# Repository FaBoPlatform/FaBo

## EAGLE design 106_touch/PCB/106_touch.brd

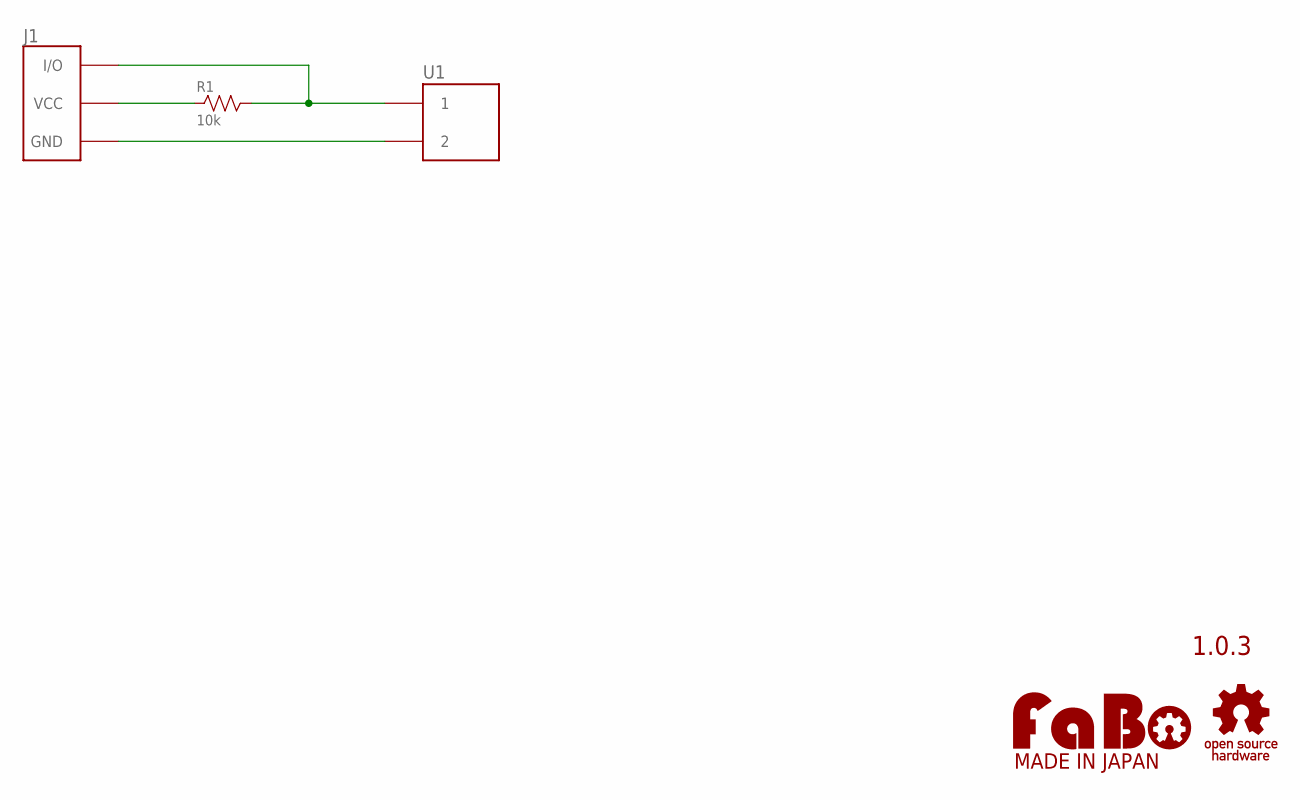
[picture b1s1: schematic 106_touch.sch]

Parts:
J1: FABO_BRICK_3PIN
R1: 10k; AXL-REGULAR
U1: FSR402-SHORT
U$2: LOGO_OSHW-M_BOTTOM; LOGO_OSHW_M_BOTTOM
U$3: LOGO_FABO-M; LOGO_FABO_MS

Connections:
GND: J1.GND, U1.P$2 (2)
unnamed: J1.I/O, R1.2, U1.P$1 (1)
unnamed: J1.VCC, R1.1

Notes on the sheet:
1.0.3

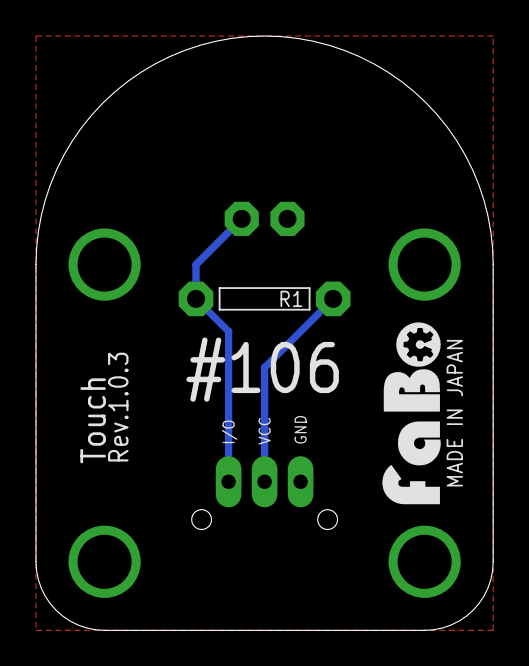
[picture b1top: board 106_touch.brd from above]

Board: 2 copper layers, 25.4 x 33.0 mm, 5 parts (0 on the bottom side), 3 nets.

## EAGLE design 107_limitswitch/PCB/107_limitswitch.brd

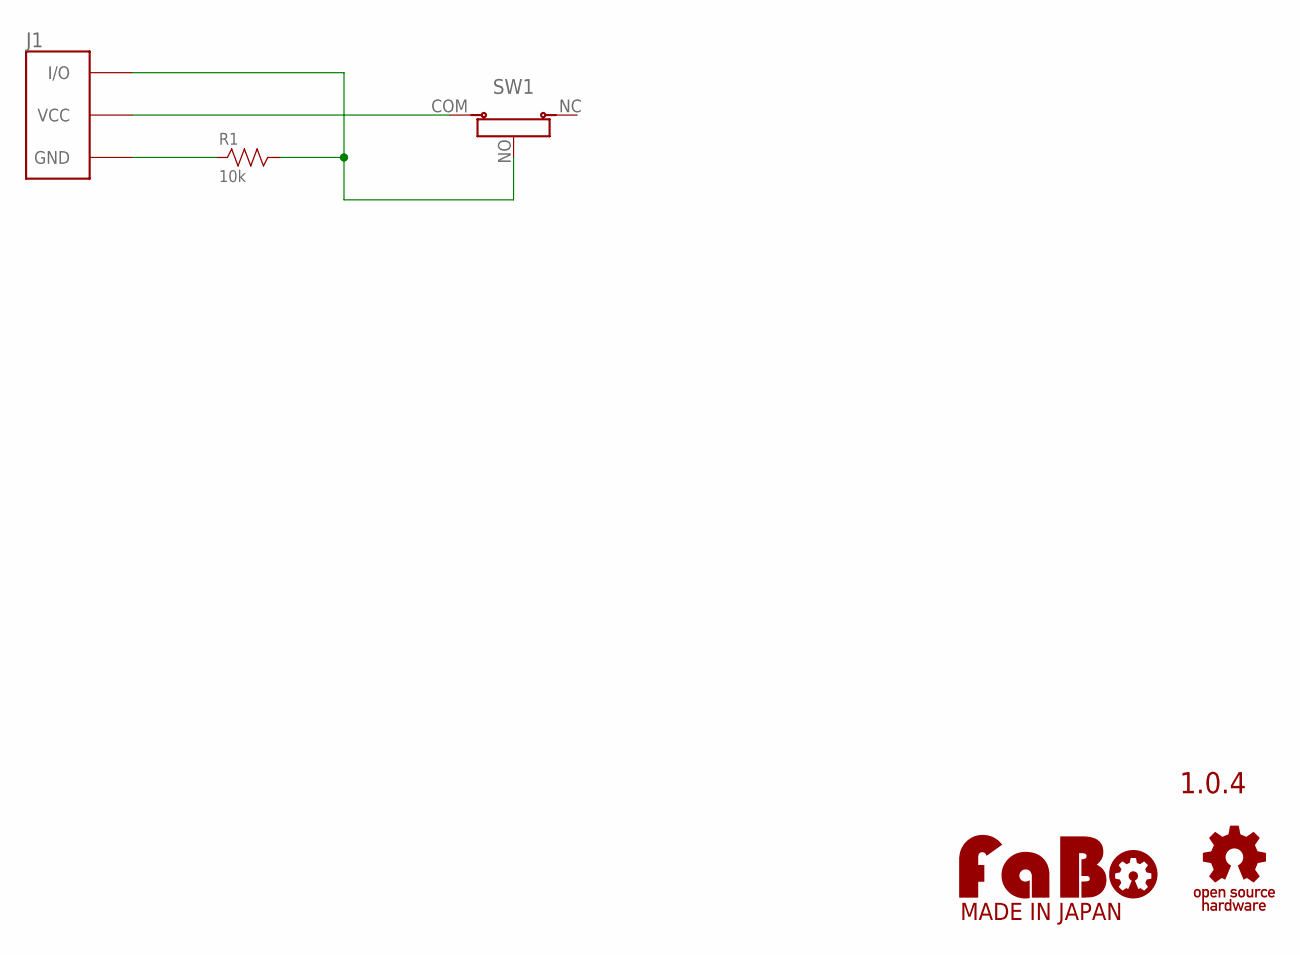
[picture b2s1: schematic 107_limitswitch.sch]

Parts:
J1: FABO_BRICK_3PIN
R1: 10k; AXL-REGULAR
SW1: LIMIT-SWITCH
U$2: LOGO_OSHW-M_BOTTOM; LOGO_OSHW_M_BOTTOM
U$4: LOGO_FABO-M; LOGO_FABO_MS

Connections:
GND: J1.GND, R1.1
unnamed: J1.VCC, SW1.COM (VCC)
unnamed: J1.I/O, R1.2, SW1.NO

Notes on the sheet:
1.0.4

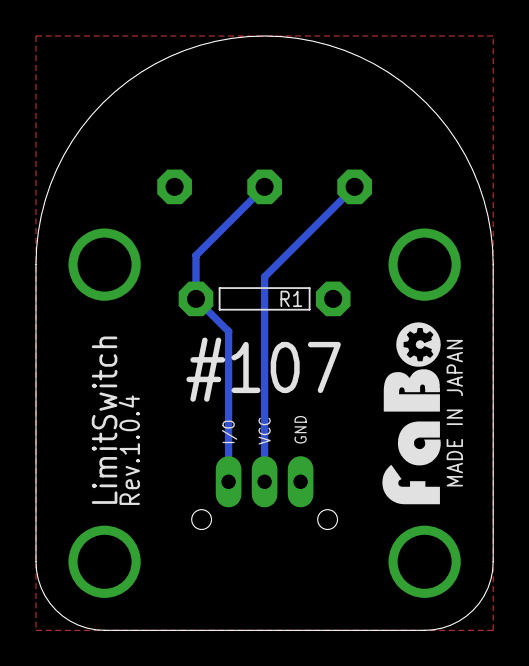
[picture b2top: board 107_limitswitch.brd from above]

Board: 2 copper layers, 25.4 x 33.0 mm, 5 parts (0 on the bottom side), 3 nets.

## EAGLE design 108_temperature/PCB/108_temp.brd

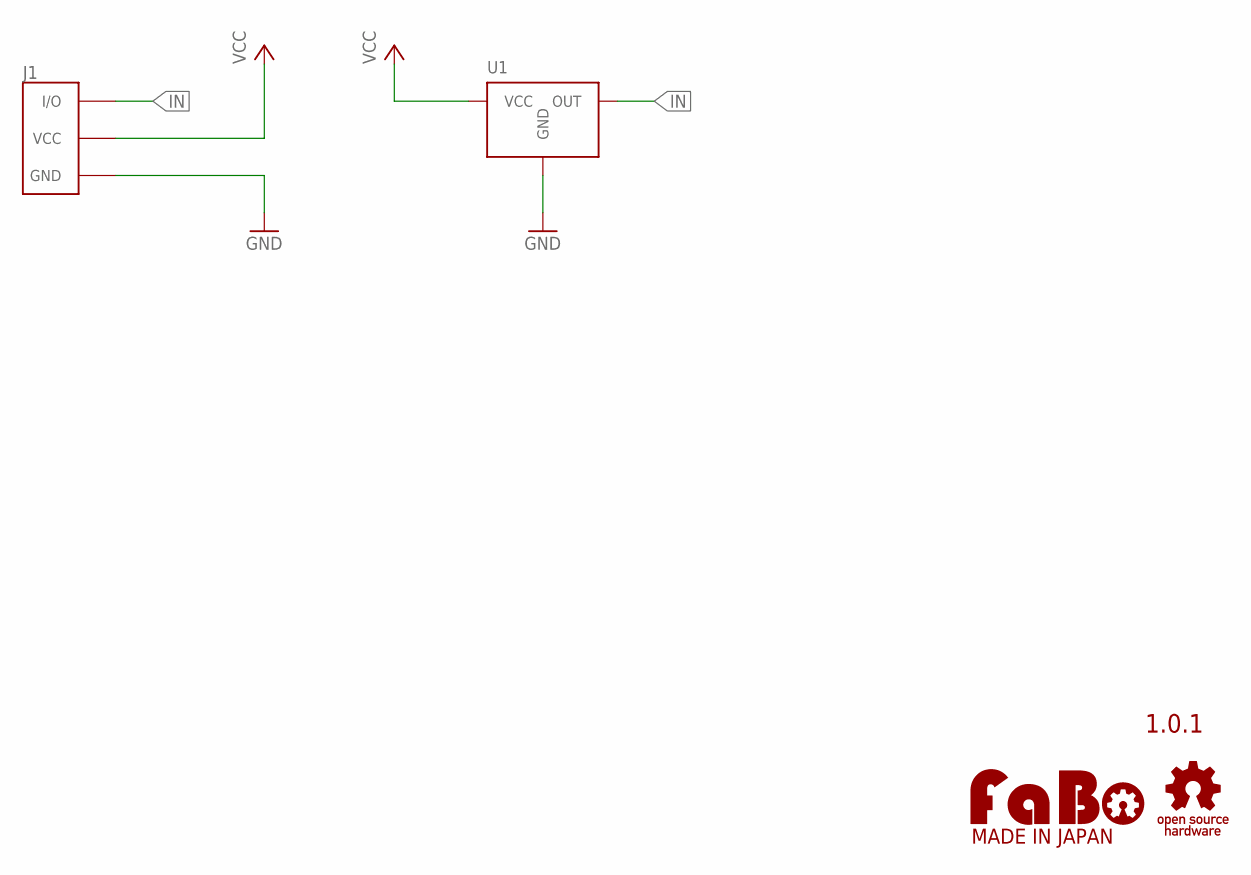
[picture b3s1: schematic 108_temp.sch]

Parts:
J1: FABO_BRICK_3PIN
U1: SENSOR-LM60-TO92; SENSOR-LM60-TO-92
U$2: LOGO_OSHW-T_M_BOTTOM; LOGO_OSHW_T_MS_BOTTOM
U$3: LOGO_FABO-M; LOGO_FABO_MS

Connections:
GND: J1.GND, U1.GND
IN: J1.IN/OUT (I/O), U1.OUT
VCC: J1.VCC, U1.VCC

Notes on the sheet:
1.0.1

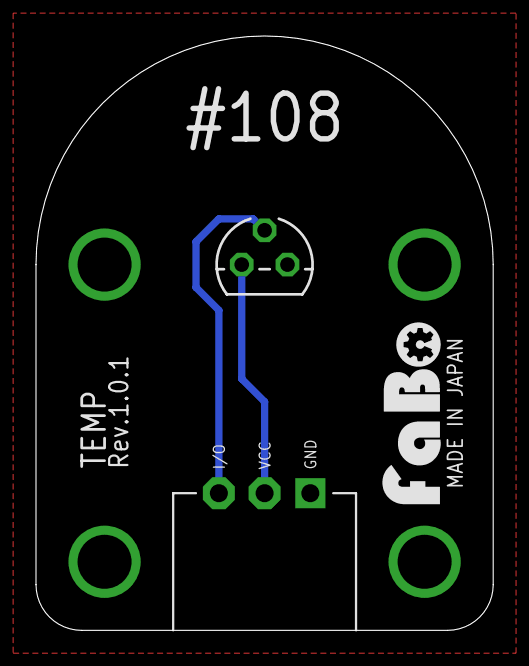
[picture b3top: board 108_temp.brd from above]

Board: 2 copper layers, 25.4 x 33.0 mm, 4 parts (0 on the bottom side), 3 nets.

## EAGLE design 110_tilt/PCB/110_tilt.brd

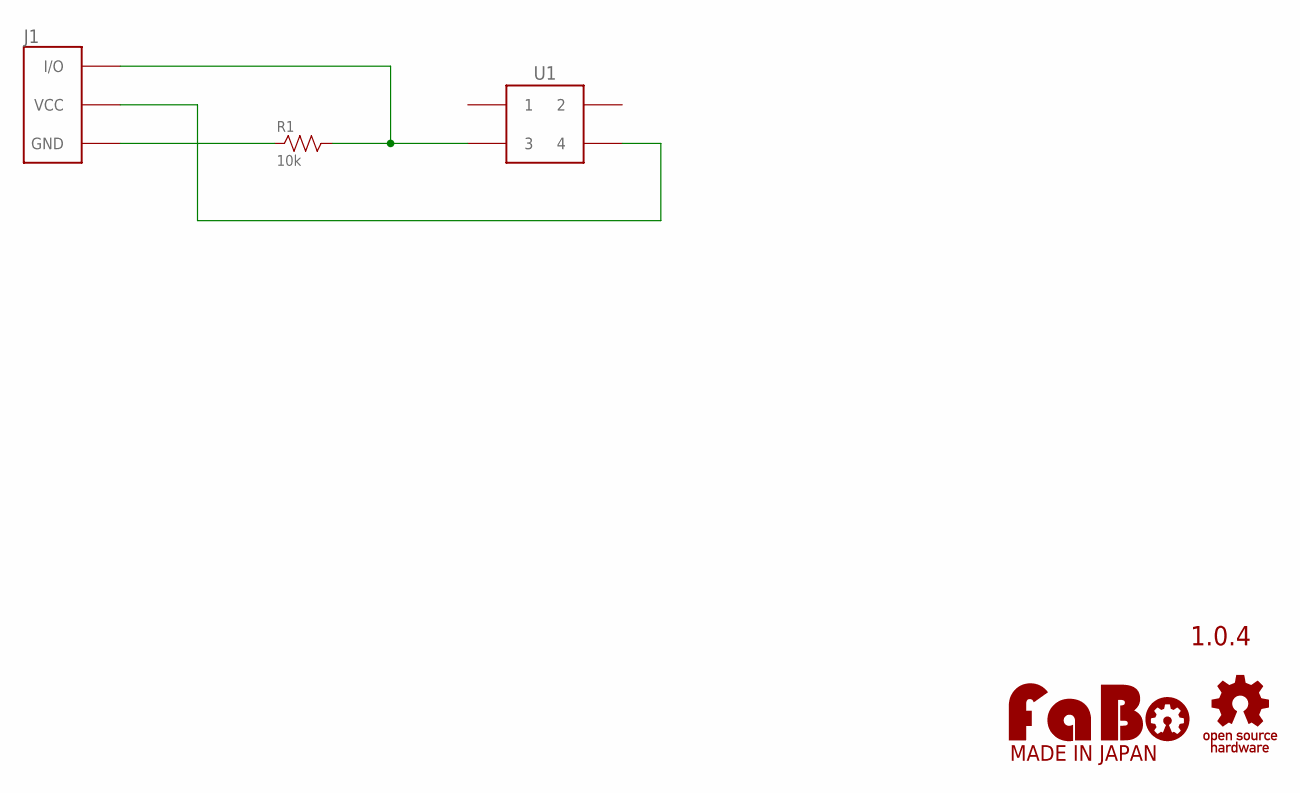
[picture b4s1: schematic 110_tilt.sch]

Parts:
J1: FABO_BRICK_3PIN
R1: 10k; AXL-REGULAR
U1: TILT; RBS040200
U$2: LOGO_OSHW-M_BOTTOM; LOGO_OSHW_M_BOTTOM
U$3: LOGO_FABO-M; LOGO_FABO_MS

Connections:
GND: J1.GND, R1.1
unnamed: J1.I/O, R1.2, U1.3
unnamed: J1.VCC, U1.4

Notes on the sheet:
1.0.4

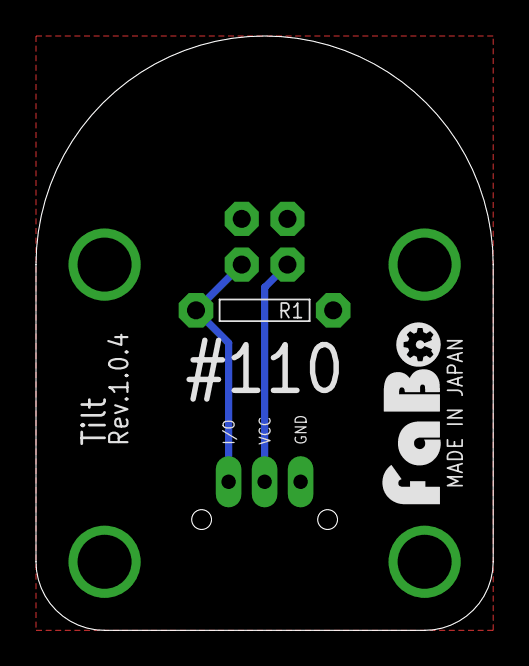
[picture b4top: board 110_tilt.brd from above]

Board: 2 copper layers, 25.4 x 33.0 mm, 5 parts (0 on the bottom side), 3 nets.

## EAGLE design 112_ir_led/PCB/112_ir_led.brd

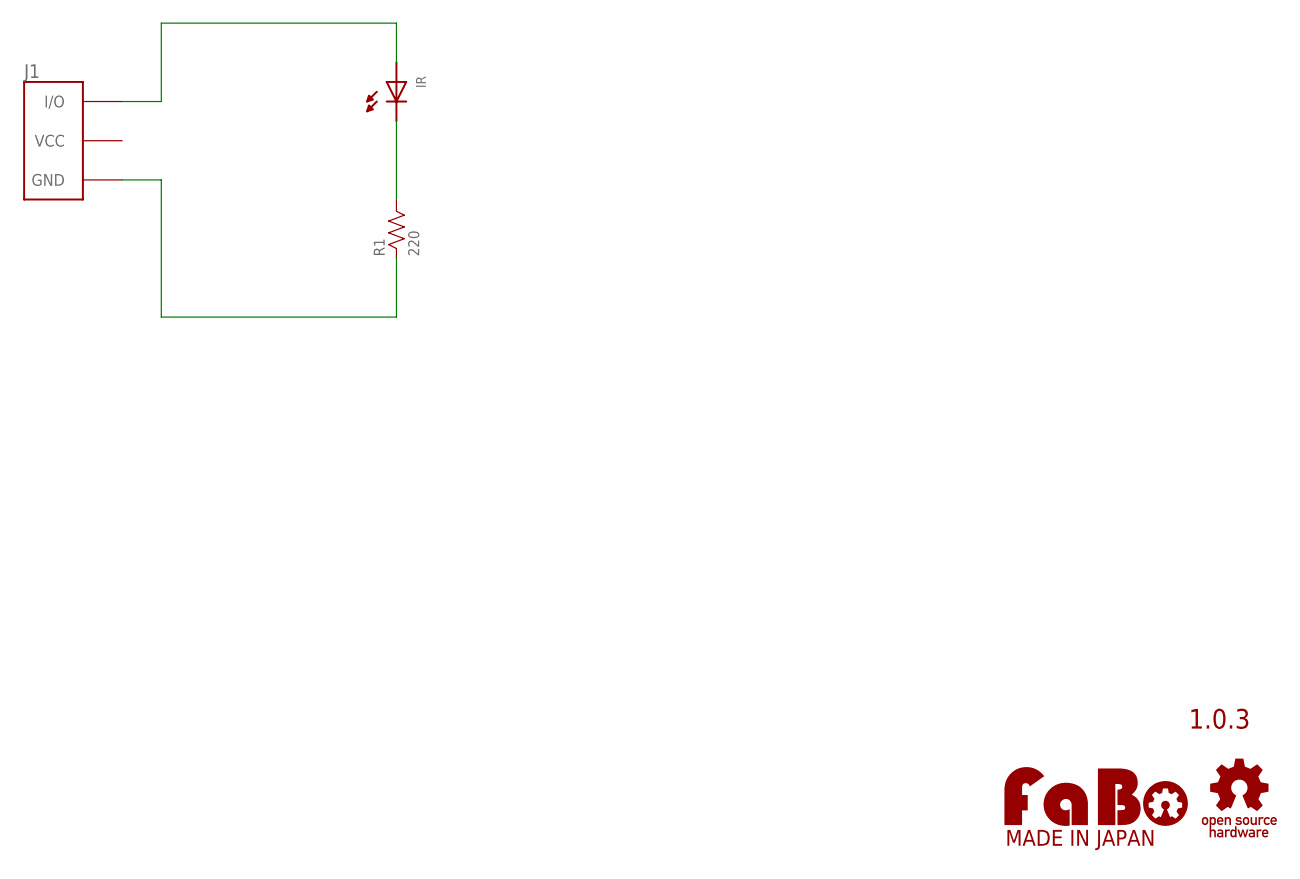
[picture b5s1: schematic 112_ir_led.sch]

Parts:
IR: LED-5MM; LED_5MM
J1: FABO_BRICK_3PIN
R1: 220; AXL-REGULAR
U$2: LOGO_FABO-M; LOGO_FABO_MS
U$3: LOGO_OSHW-M_BOTTOM; LOGO_OSHW_M_BOTTOM

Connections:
GND: J1.GND, R1.1
unnamed: IR.A (ANODE), J1.I/O
unnamed: IR.K (CATHODE), R1.2

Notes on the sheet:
1.0.3

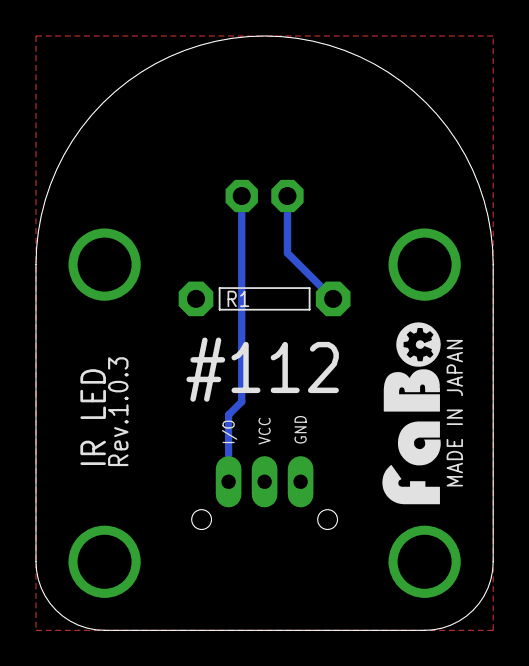
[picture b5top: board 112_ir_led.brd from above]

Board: 2 copper layers, 25.4 x 33.0 mm, 5 parts (0 on the bottom side), 3 nets.

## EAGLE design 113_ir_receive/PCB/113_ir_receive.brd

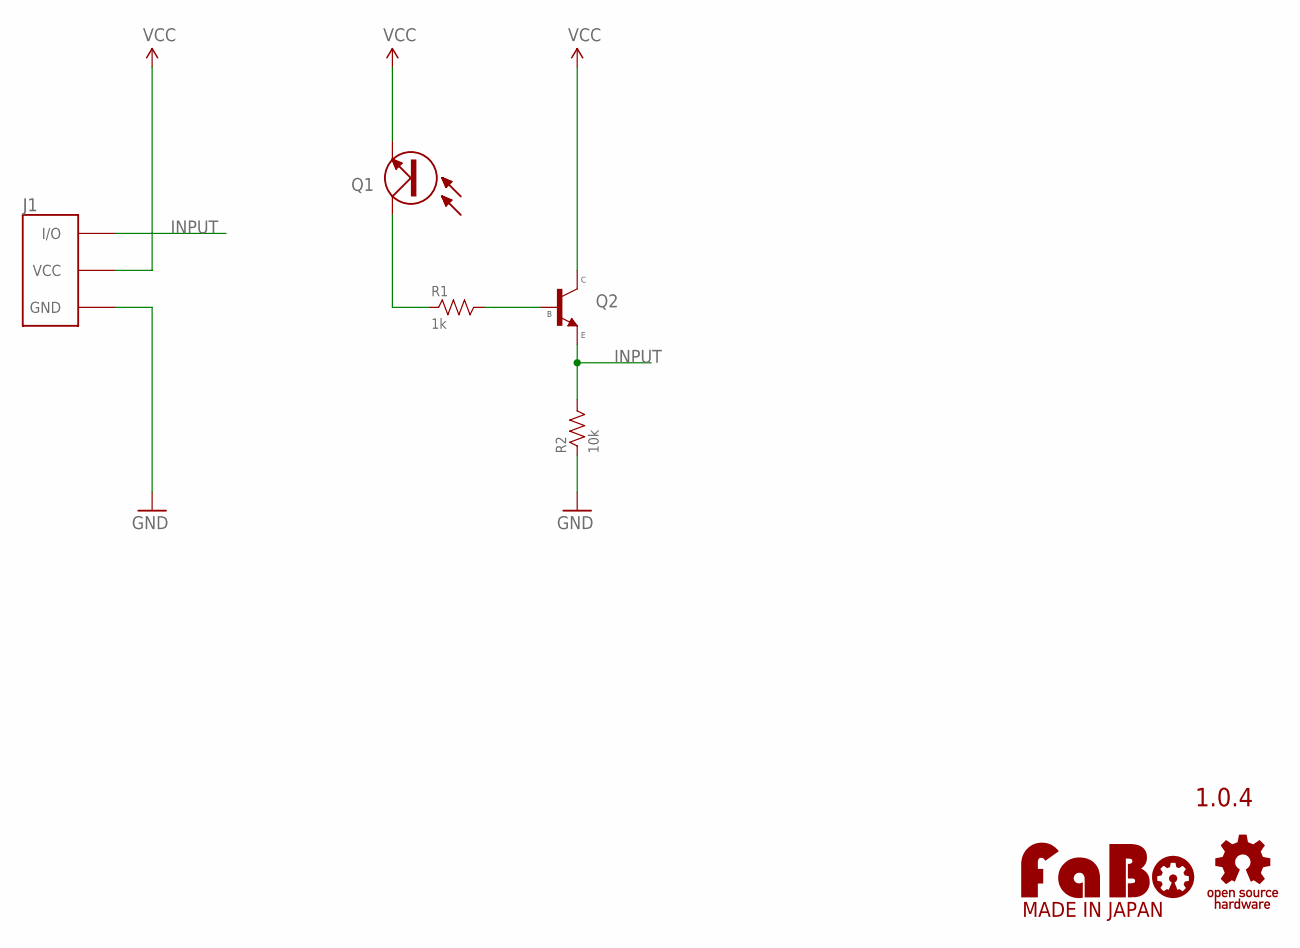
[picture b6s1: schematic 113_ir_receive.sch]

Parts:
J1: FABO_BRICK_3PIN
Q1: L-51ROPT1D1; LED-5MM
Q2: NPN-2SC1815; TO-92
R1: 1k; AXL-REGULAR
R2: 10k; AXL-REGULAR
U$5: LOGO_FABO-M; LOGO_FABO_MS
U$6: LOGO_OSHW-M_BOTTOM; LOGO_OSHW_M_BOTTOM

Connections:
GND: J1.GND, R2.1
INPUT: J1.I/O, Q2.1 (E), R2.2
unnamed: Q1.K (C), R1.1
unnamed: Q2.3 (B), R1.2
VCC: J1.VCC, Q1.A (E), Q2.2 (C)

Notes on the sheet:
1.0.4

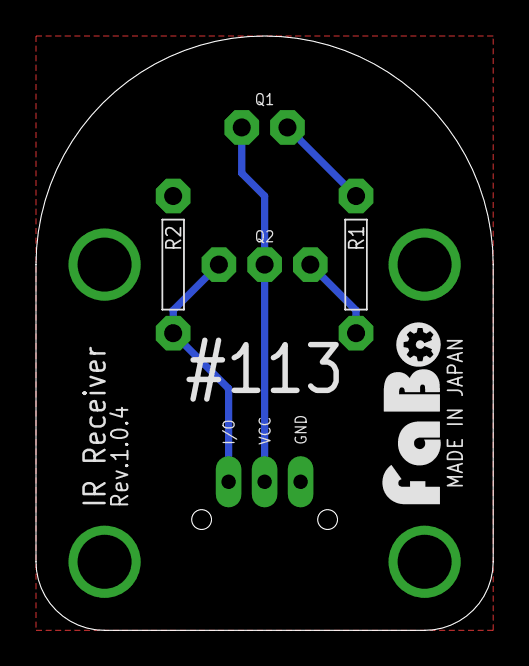
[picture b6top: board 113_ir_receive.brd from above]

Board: 2 copper layers, 25.4 x 33.0 mm, 7 parts (0 on the bottom side), 5 nets.

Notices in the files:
parts and their libraries:
FaBo-Template: Released under the Creative Commons Attribution-ShareAlike 4.0 License
https://creativecommons.org/licenses/by-sa/4.0
FaBo-etc: Released under the Creative Commons
